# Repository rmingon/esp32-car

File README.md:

# ESP32 RC Car with Web Control

This project is a simple DIY RC car built using an **ESP32**, dual motor driver (**MX1508**), and a **web-based controller interface built with Angular**. The ESP32 acts as the brain, controlling two DC motors and hosting a lightweight web server for real-time control via Wi-Fi.

## 🚗 Features

- 🔌 Dual motor control using the MX1508 driver
- 🌐 Wi-Fi hosted Angular web app for control (no mobile app needed!)
- 🎮 Real-time forward, backward, left, right, and stop commands
- ⚙️ Easily customizable for future sensors (e.g., ultrasonic, line-following)
- 💡 Minimal wiring, compact build

## 🛠 Hardware Used

- ESP32 wroom
- MX1508 Dual Motor Driver
- 2x DC Motors (TT Gear motors or similar)
- Power Supply (Li-ion battery or USB power bank)
- Chassis, wheels, jumper wires

## 🧰 Software Stack

- ESP32 (Arduino/C++ firmware)
- Angular (Web UI for car control)
- HTML / CSS / JS (Frontend)
- WebSockets or HTTP endpoints (for command communication)

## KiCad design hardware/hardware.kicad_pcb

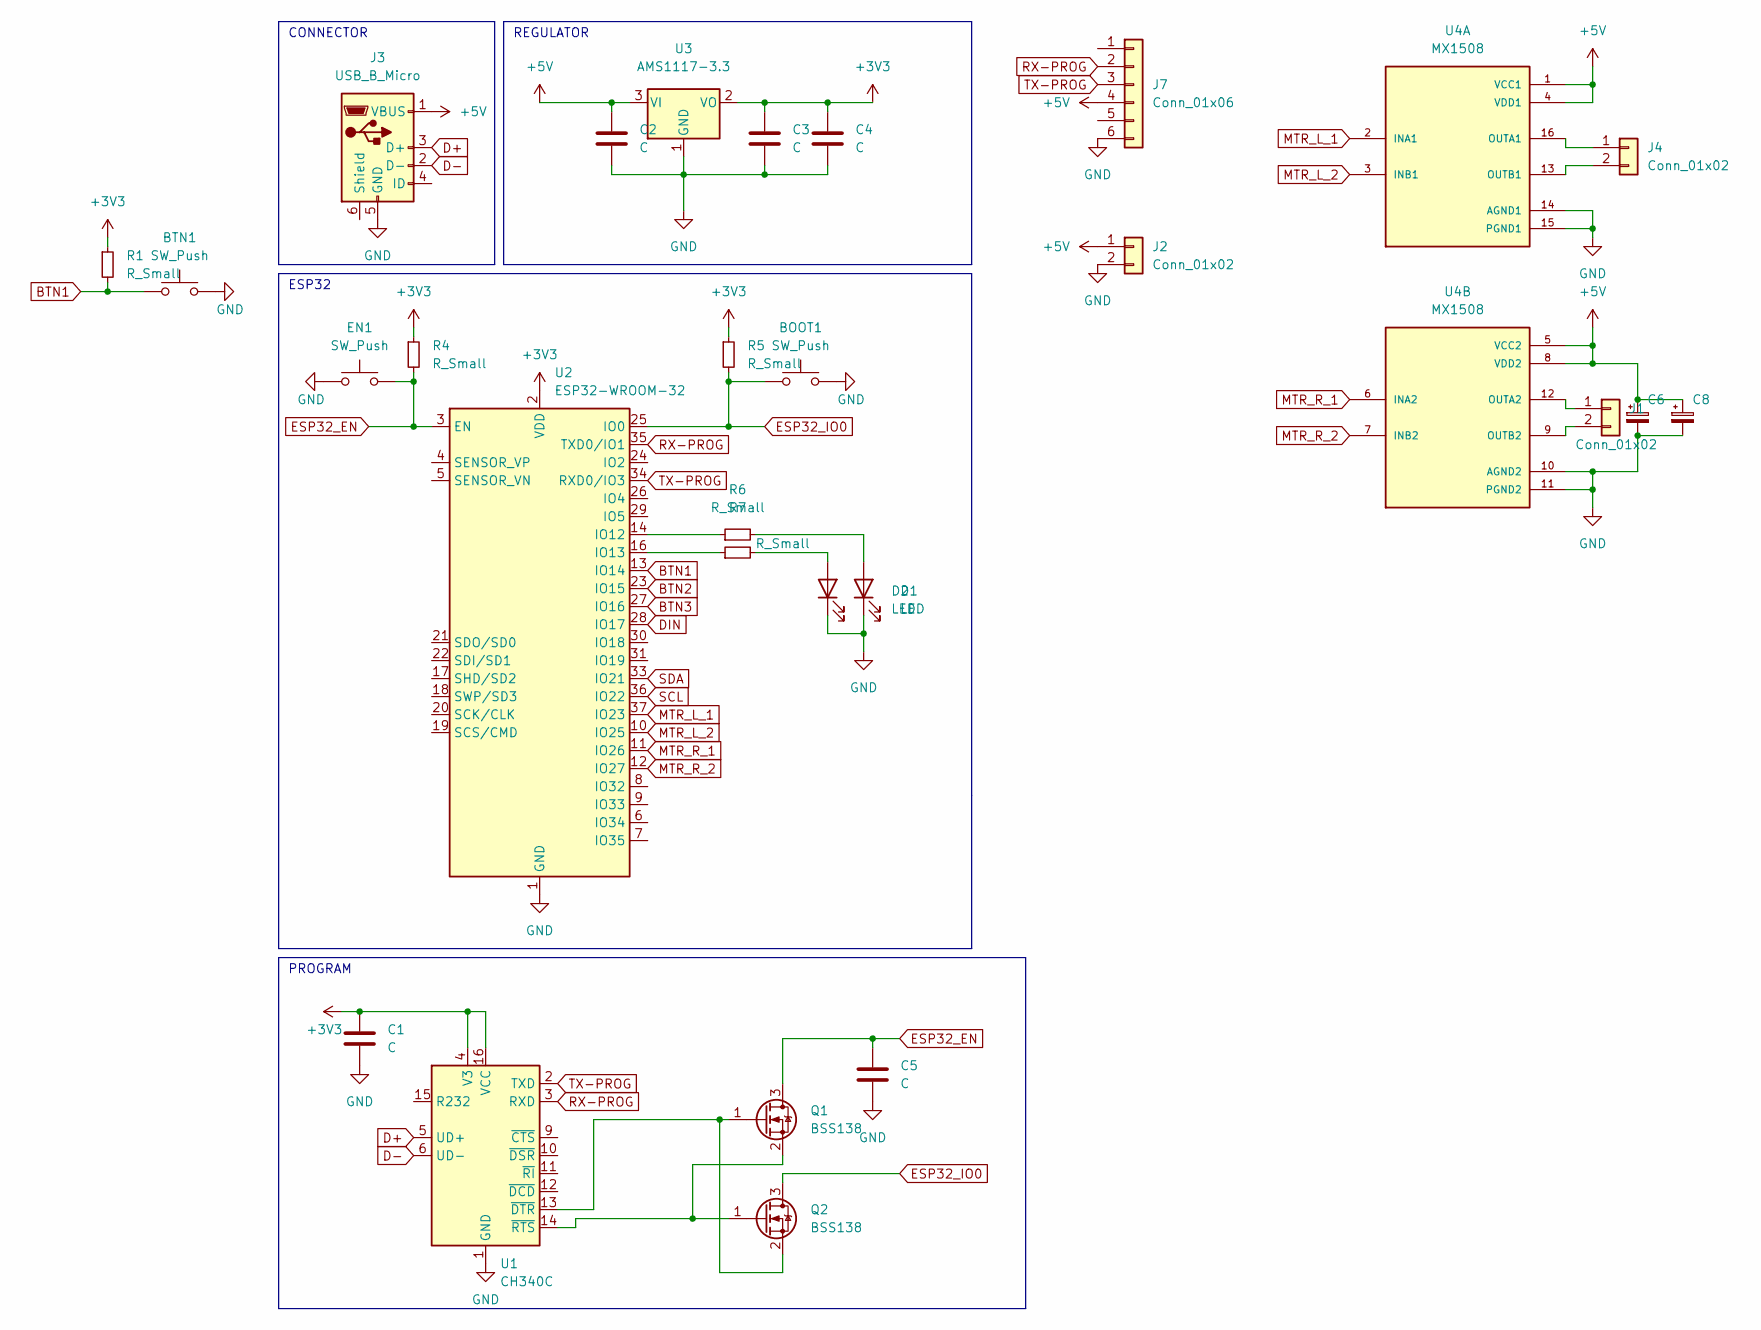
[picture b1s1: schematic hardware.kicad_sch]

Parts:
BOOT1: SW_Push; SW_SPST_FSMSM
BTN1: SW_Push; SW_SPST_FSMSM
C1, C2, C3, C4, C5: C; C_0603_1608Metric
C6, C8: C_Polarized_Small; CP_Elec_6.3x4.9
D1, D2: LED; LED_0603_1608Metric
EN1: SW_Push; SW_SPST_FSMSM
J1, J2, J4: Conn_01x02; PinSocket_1x02_P2.54mm_Vertical
J3: USB_B_Micro; USB_Micro-B_Molex-105017-0001
J7: Conn_01x06; PinHeader_1x06_P2.54mm_Vertical
Q1, Q2: BSS138; SOT-23
R1, R4, R5, R6, R7: R_Small; R_0603_1608Metric
U1: CH340C; SOIC-16_3.9x9.9mm_P1.27mm
U2: ESP32-WROOM-32
U3: AMS1117-3.3; SOT-223-3_TabPin2
U4: MX1508; SOIC-16_3.9x9.9mm_P1.27mm

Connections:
+3V3: C1.1, C3.1, C4.1, R1.1, R4.1, R5.1, U1.4 (V3), U1.16 (VCC), U2.2 (VDD), U3.2 (VO)
+5V: C2.1, C6.1, C8.1, J2.1, J3.1 (VBUS), J7.4, U3.3 (VI), U4.1 (VCC1), U4.4 (VDD1), U4.5 (VCC2), U4.8 (VDD2)
BTN1: BTN1.1, R1.2, U2.13 (IO14)
BTN2: U2.23 (IO15)
BTN3: U2.27 (IO16)
D+: J3.3 (D+), U1.5 (UD+)
D-: J3.2 (D-), U1.6 (UD-)
DIN: U2.28 (IO17)
ESP32_EN: C5.1, EN1.2, Q1.3 (D), R4.2, U2.3 (EN)
ESP32_IO0: BOOT1.1, Q2.3 (D), R5.2, U2.25 (IO0)
GND: BOOT1.2, BTN1.2, C1.2, C2.2, C3.2, C4.2, C5.2, C6.2, C8.2, D1.1 (K), D2.1 (K), EN1.1, J2.2, J3.5 (GND), J7.6, U1.1 (GND), U2.1 (GND), U2.15 (GND), U2.38 (GND), U2.39 (GND), U3.1 (GND), U4.10 (AGND2), U4.11 (PGND2), U4.14 (AGND1), U4.15 (PGND1)
MTR_L_1: U2.37 (IO23), U4.2 (INA1)
MTR_L_2: U2.10 (IO25), U4.3 (INB1)
MTR_R_1: U2.11 (IO26), U4.6 (INA2)
MTR_R_2: U2.12 (IO27), U4.7 (INB2)
unnamed: D1.2 (A), R7.2
unnamed: D2.2 (A), R6.2
unnamed: J1.1, U4.12 (OUTA2)
unnamed: J1.2, U4.9 (OUTB2)
unnamed: J4.1, U4.16 (OUTA1)
unnamed: J4.2, U4.13 (OUTB1)
unnamed: Q1.1 (G), Q2.2 (S), U1.13 (~DTR)
unnamed: Q1.2 (S), Q2.1 (G), U1.14 (~RTS)
unnamed: R6.1, U2.14 (IO12)
unnamed: R7.1, U2.16 (IO13)
RX-PROG: J7.2, U1.3 (RXD), U2.35 (TXD0/IO1)
SCL: U2.36 (IO22)
SDA: U2.33 (IO21)
TX-PROG: J7.3, U1.2 (TXD), U2.34 (RXD0/IO3)

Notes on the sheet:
REGULATOR
CONNECTOR
ESP32
PROGRAM

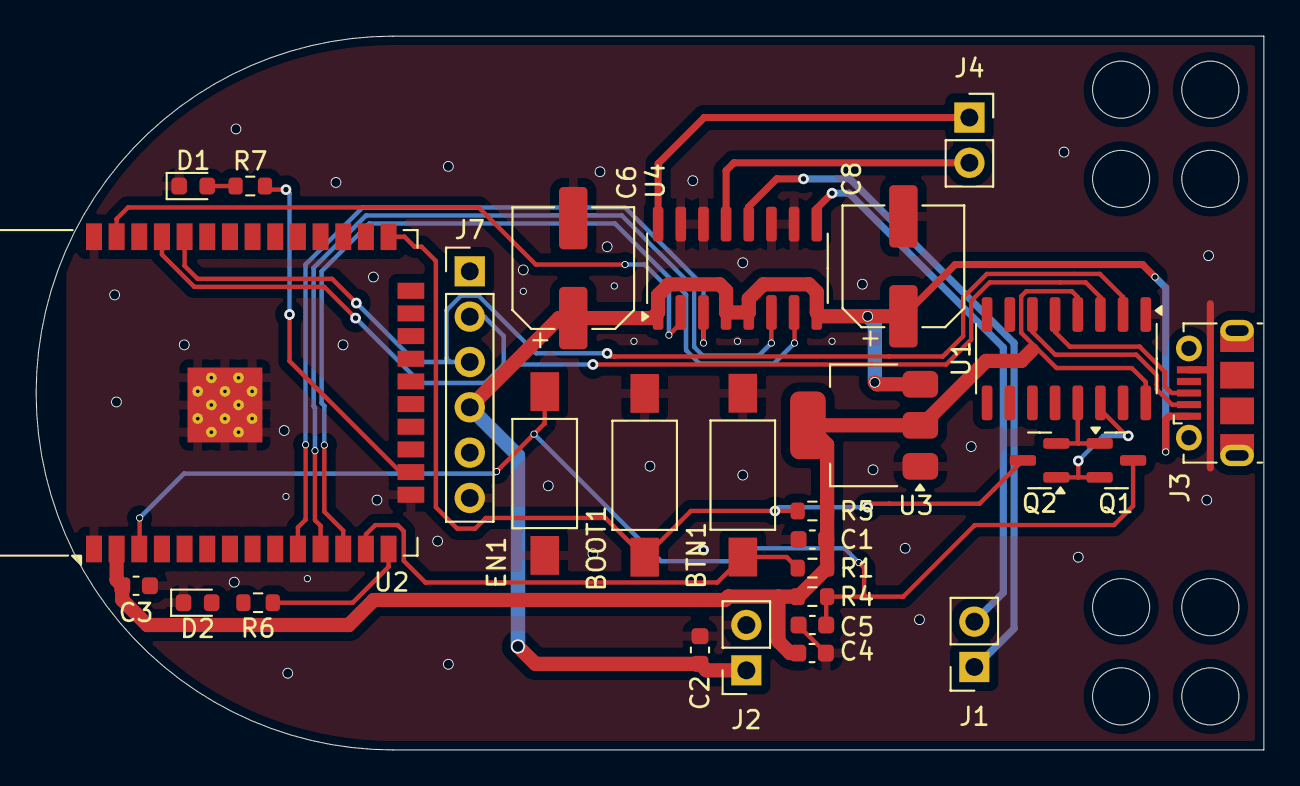
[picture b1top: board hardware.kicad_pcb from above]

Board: 2 copper layers, 68.8 x 40.0 mm, 28 parts (0 on the bottom side), 24 nets.

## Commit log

2025-03-08 add schematic esp32 + mx1508
2025-03-08 add ftdi
2025-03-09 place componants + mounting holes
2025-03-09 wiring pcb
2025-03-12 add wiring mx1508 + vcc headers connector
2025-03-23 first software commit
2025-03-24 add front
2025-04-08 add real picutre of car
